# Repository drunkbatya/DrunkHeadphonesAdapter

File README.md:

# DrunkHeadphonesAdapter

## About

Yet another headphone adapter for mobile phones without 3.5mm jack..

I fucking hate the assholes who thought removing the headphone jack was a good idea.

This device integrated into a phone case and allows you to charge phone while listening to music. Charging is limited to 60-watt PD, USB PD Fast Role Swap is also supported, so theoretically, music playback shouldn't be interrupted when connecting or disconnecting the charger (currently untested).

The board has a physical switch that connects the phone USB data lines directly to the charger port. It also has two internal DIP switches: one to disable the microphone (by shorting Ring2 and Sleeve) and another to disable headphone detection.

The adapter uses readily available components and is designed for JLCPCB SMT assembly.

## Features
- CS43131 DAC with 24bit 96khz with independent oscillators for 24.576MHz and 22.5792MHz
- ES8327 codec with 24bit 48khz ADC only used for microphone
- STM32G0B1VCT6 acts as both USB-I2S converter and UCPD controller
- 60W PD with Fast Role Swap to prevent pausing music when connecting or disconnecting the charger
- Dual-role charger USB-C port, capable of both sinking and sourcing power
- CTIA headset pinout only, but pin 3 and 4 can be shorted via DIP switch
- Headset button decoding and forwarding to the phone as HID events
- UAC2+HID API, both Android and IOS are supported
- A lot of ESD protection on all external pins

## Firmware
HAL and arcitecture core is based on ported [Flipper Zero OS](https://github.com/flipperdevices/flipperzero-firmware)

### Building
```bash
git submodule update --init --recursive
make
```

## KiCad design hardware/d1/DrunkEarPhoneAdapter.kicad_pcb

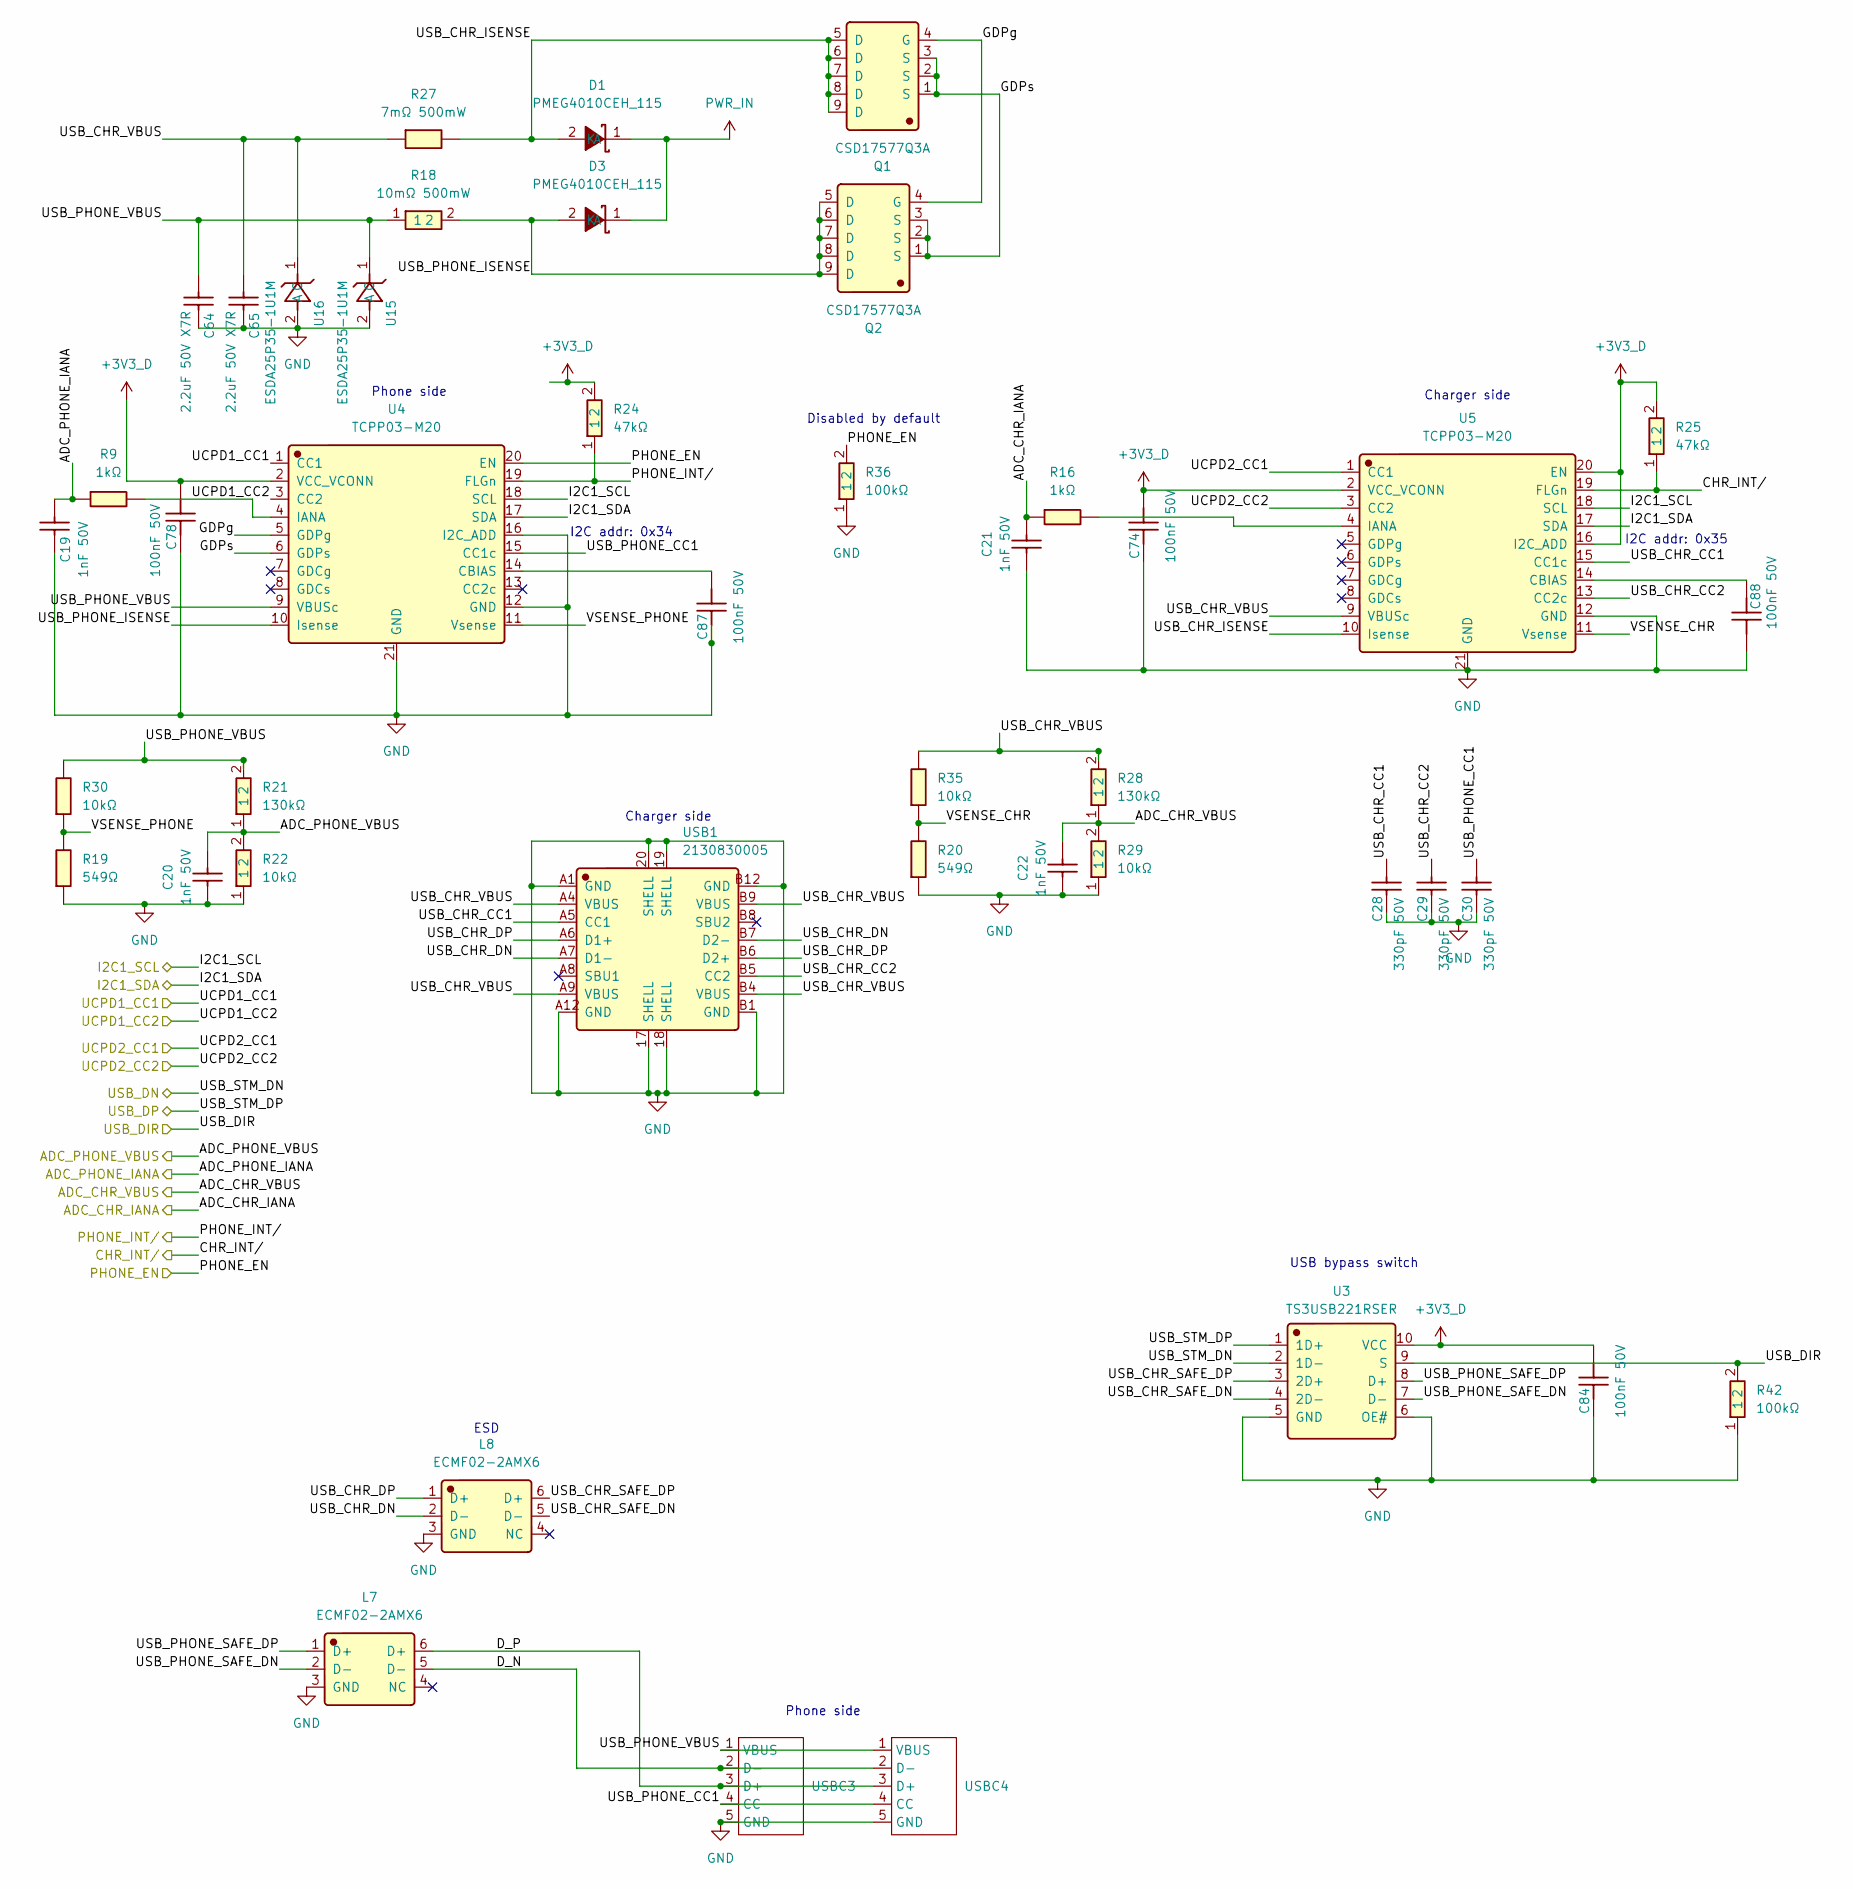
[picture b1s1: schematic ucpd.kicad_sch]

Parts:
C19, C20, C21, C22: 1nF 50V; C_0402_1005Metric; Manufacturer Part 0402B102K500NT; LCSC C1523
C28, C29, C30: 330pF 50V; C_0603_1608Metric; Manufacturer Part CL10C331JB8NNNC; LCSC C1664
C64, C65: 2.2uF 50V X7R; C_1206_3216Metric; Manufacturer Part CL31B225KBHNNNE; LCSC C50254
C74, C78, C84, C87, C88: 100nF 50V; C_0402_1005Metric; Manufacturer Part CL05B104KB54PNC; LCSC C307331
D1, D3: PMEG4010CEH_115; D_SOD-123F; Manufacturer Part PMEG4010CEH,115; LCSC C193342
L7, L8: ECMF02-2AMX6; Manufacturer Part ECMF02-2AMX6; LCSC C2651144
Q1, Q2: CSD17577Q3A; Manufacturer Part CSD17577Q3A; LCSC C201632
R9, R16: 1kΩ; R_0402_1005Metric; Manufacturer Part 0402WGF1001TCE; LCSC C11702
R18: 10mΩ 500mW; R_0805_2012Metric; Manufacturer Part ERJ6BWFR010V; LCSC C409060
R19, R20: 549Ω; R_0603_1608Metric; Manufacturer Part 0603WAF5490T5E; LCSC C23079
R21, R28: 130kΩ; R_0402_1005Metric; Manufacturer Part RC0402FR-07130KL; LCSC C93946
R22, R29: 10kΩ; R_0402_1005Metric; Manufacturer Part 0402WGF1002TCE; LCSC C25744
R24, R25: 47kΩ; R_0402_1005Metric; Manufacturer Part 0402WGF4702TCE; LCSC C25792
R27: 7mΩ 500mW; R_0805_2012Metric; Manufacturer Part HoYLR0805-1/2W-7mR-1%; LCSC C22450691
R30, R35: 10kΩ; R_0603_1608Metric; Manufacturer Part 0603WAF1002T5E; LCSC C25804
R36, R42: 100kΩ; 0402WGF1003TCE; Manufacturer Part 0402WGF1003TCE; LCSC C25741
U3: TS3USB221RSER; Manufacturer Part TS3USB221RSER; LCSC C130085
U4, U5: TCPP03-M20; Manufacturer Part TCPP03-M20; LCSC C3662955
U15, U16: ESDA25P35-1U1M; ESDA25P35-1U1M_C19829649; Manufacturer Part ESDA25P35-1U1M; LCSC C19829649
USB1: 2130830005; Manufacturer Part 2130830005; LCSC C2839029
USBC3, USBC4: USBC_EXT_5P

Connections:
+3V3_D: C74.2, C78.2, C84.2, R24.2, R25.2, U3.10 (VCC), U4.2 (VCC_VCONN), U5.2 (VCC_VCONN), U5.16 (I2C_ADD), U5.20 (EN); also elsewhere on the board
/adc/I2C_SCL: U4.18 (SCL), U5.18 (SCL); also elsewhere on the board
/adc/I2C_SDA: U4.17 (SDA), U5.17 (SDA); also elsewhere on the board
/mcu/ADC1_IN0: C19.2, R9.1; also elsewhere on the board
/mcu/ADC1_IN1: C20.2, R21.1, R22.2; also elsewhere on the board
/mcu/ADC1_IN2: C21.2, R16.1; also elsewhere on the board
/mcu/ADC1_IN3: C22.2, R28.1, R29.2; also elsewhere on the board
/mcu/GPIO_EXTI2: R24.1, U4.19 (FLGn); also elsewhere on the board
/mcu/GPIO_EXTI3: R25.1, U5.19 (FLGn); also elsewhere on the board
/mcu/PHONE_EN: R36.2, U4.20 (EN); also elsewhere on the board
/mcu/UCPD1_CC1: U4.1 (CC1); also elsewhere on the board
/mcu/UCPD1_CC2: U4.3 (CC2); also elsewhere on the board
/mcu/UCPD2_CC1: U5.1 (CC1); also elsewhere on the board
/mcu/UCPD2_CC2: U5.3 (CC2); also elsewhere on the board
/mcu/USB_DIR: R42.2, U3.9 (S); also elsewhere on the board
/mcu/USB_DN: U3.2 (1D-); also elsewhere on the board
/mcu/USB_DP: U3.1 (1D+); also elsewhere on the board
/ucpd/D_N: L7.5 (D-), USBC3.2 (D-), USBC4.2 (D-)
/ucpd/D_P: L7.6 (D+), USBC3.3 (D+), USBC4.3 (D+)
/ucpd/GDPg: Q1.4 (G), Q2.4 (G), U4.5 (GDPg)
/ucpd/GDPs: Q1.1 (S), Q1.2 (S), Q1.3 (S), Q2.1 (S), Q2.2 (S), Q2.3 (S), U4.6 (GDPs)
/ucpd/USB_CHR_CC1: C28.2, U5.15 (CC1c), USB1.A5 (CC1)
/ucpd/USB_CHR_CC2: C29.2, U5.13 (CC2c), USB1.B5 (CC2)
/ucpd/USB_CHR_DN: L8.2 (D-), USB1.A7 (D1-), USB1.B7 (D2-)
/ucpd/USB_CHR_DP: L8.1 (D+), USB1.A6 (D1+), USB1.B6 (D2+)
/ucpd/USB_CHR_ISENSE: D1.2 (A), Q1.5 (D), Q1.6 (D), Q1.7 (D), Q1.8 (D), Q1.9 (D), R27.2, U5.10 (Isense)
/ucpd/USB_CHR_SAFE_DN: L8.5 (D-), U3.4 (2D-)
/ucpd/USB_CHR_SAFE_DP: L8.6 (D+), U3.3 (2D+)
/ucpd/USB_CHR_VBUS: C65.2, R27.1, R28.2, R35.2, U5.9 (VBUSc), U16.1 (C), USB1.A4 (VBUS), USB1.A9 (VBUS), USB1.B4 (VBUS), USB1.B9 (VBUS)
/ucpd/USB_PHONE_CC1: C30.2, U4.15 (CC1c), USBC3.4 (CC), USBC4.4 (CC)
/ucpd/USB_PHONE_ISENSE: D3.2 (A), Q2.5 (D), Q2.6 (D), Q2.7 (D), Q2.8 (D), Q2.9 (D), R18.2, U4.10 (Isense)
/ucpd/USB_PHONE_SAFE_DN: L7.2 (D-), U3.7 (D-)
/ucpd/USB_PHONE_SAFE_DP: L7.1 (D+), U3.8 (D+)
/ucpd/USB_PHONE_VBUS: C64.2, R18.1, R21.2, R30.2, U4.9 (VBUSc), U15.1 (C), USBC3.1 (VBUS), USBC4.1 (VBUS)
/ucpd/VSENSE_CHR: R20.2, R35.1, U5.11 (Vsense)
/ucpd/VSENSE_PHONE: R19.2, R30.1, U4.11 (Vsense)
GND: C19.1, C20.1, C21.1, C22.1, C28.1, C29.1, C30.1, C64.1, C65.1, C74.1, C78.1, C84.1, C87.1, C88.2, L7.3 (GND), L8.3 (GND), R19.1, R20.1, R22.1, R29.1, R36.1, R42.1, U3.5 (GND), U3.6 (OE#), U4.12 (GND), U4.16 (I2C_ADD), U4.21 (GND), U5.12 (GND), U5.21 (GND), U15.2 (A), U16.2 (A), USB1.17 (SHELL), USB1.18 (SHELL), USB1.19 (SHELL), USB1.20 (SHELL), USB1.A1 (GND), USB1.A12 (GND), USB1.B1 (GND), USB1.B12 (GND), USBC3.5 (GND), USBC4.5 (GND); also elsewhere on the board
unnamed: C87.2, U4.14 (CBIAS)
unnamed: R9.2, U4.4 (IANA)
unnamed: C88.1, U5.14 (CBIAS)
unnamed: R16.2, U5.4 (IANA)
PWR_IN: D1.1 (K), D3.1 (K); also elsewhere on the board

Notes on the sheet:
I2C addr: 0x34
Charger side
I2C addr: 0x35
Disabled by default
USB bypass switch
Phone side
ESD

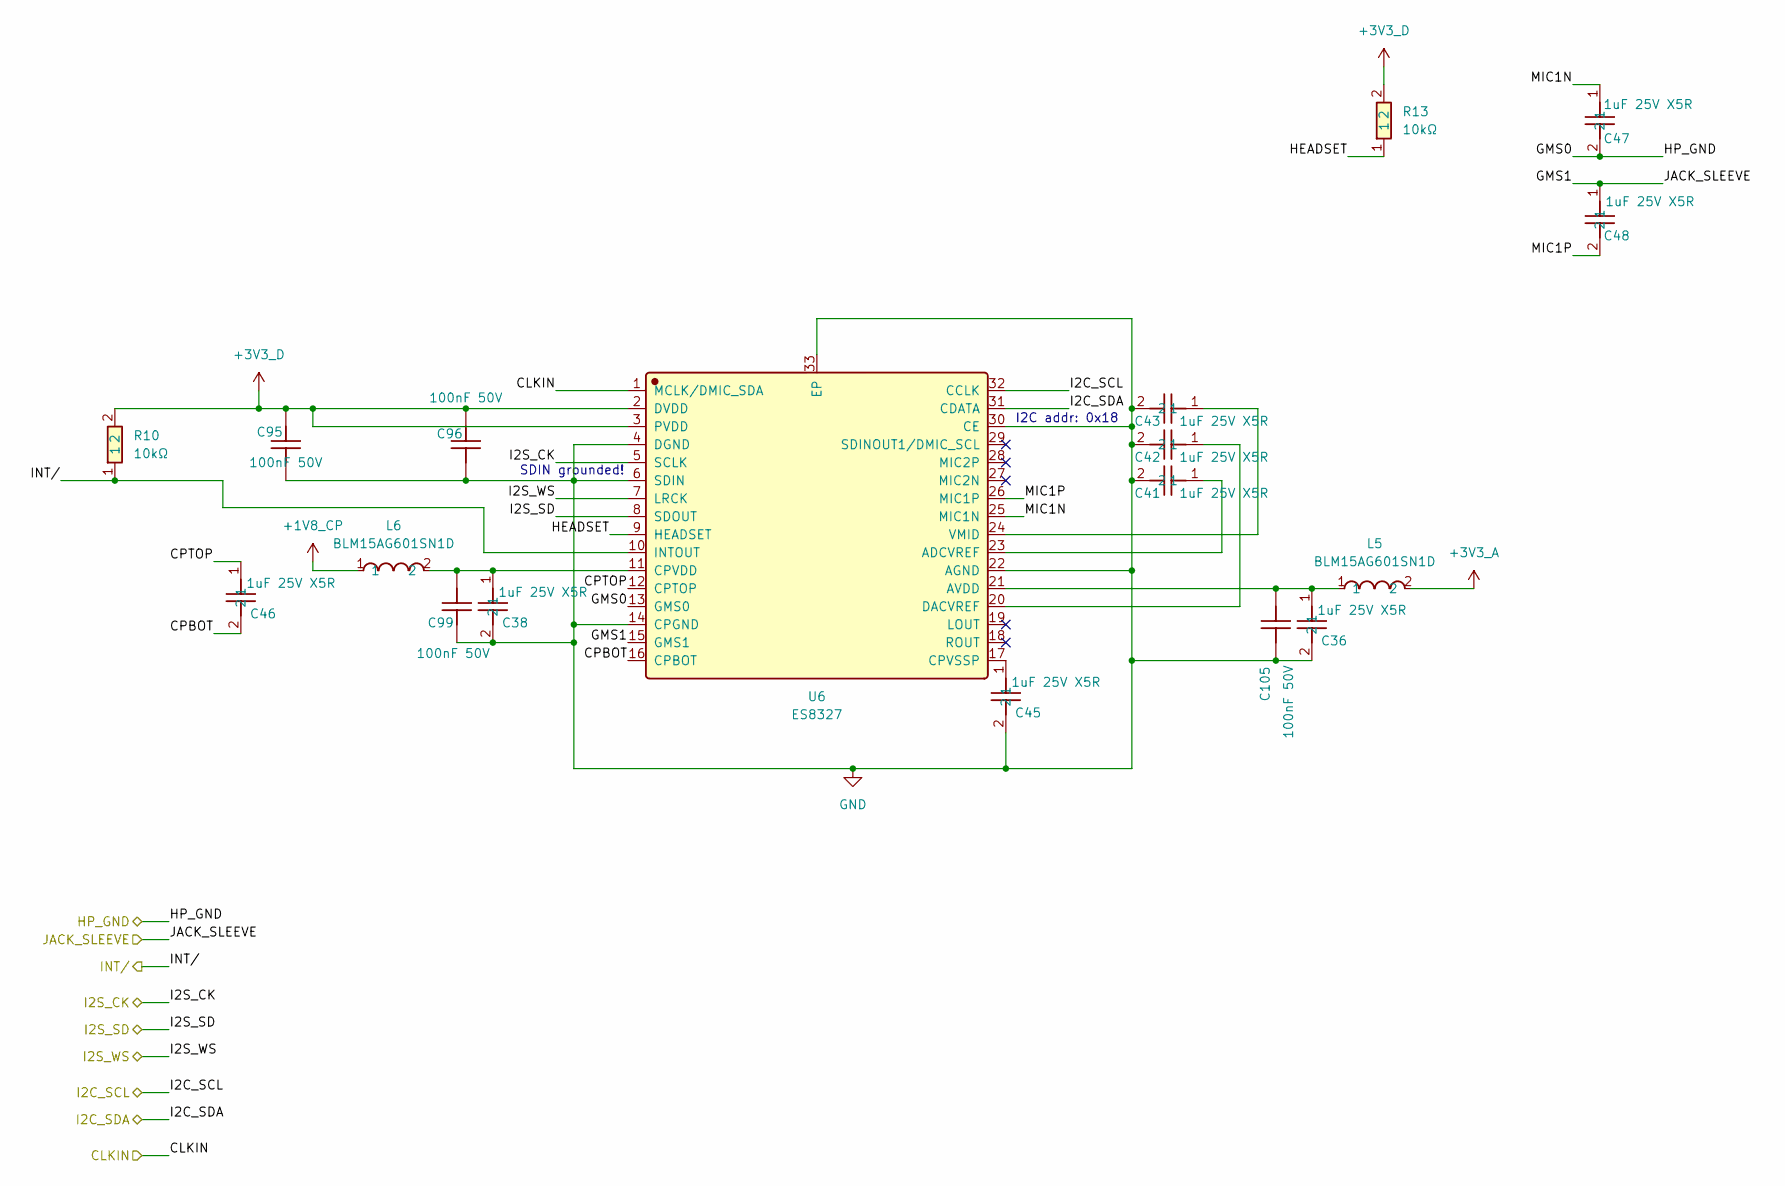
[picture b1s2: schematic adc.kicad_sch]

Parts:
C36, C38, C41, C42, C43, C45, C46, C47, C48: 1uF 25V X5R; CL05A105KA5NQNC; Manufacturer Part CL05A105KA5NQNC; LCSC C52923
C95, C96, C99, C105: 100nF 50V; C_0402_1005Metric; Manufacturer Part CL05B104KB54PNC; LCSC C307331
L5, L6: BLM15AG601SN1D; Manufacturer Part BLM15AG601SN1D; LCSC C76884
R10, R13: 10kΩ; R_0402_1005Metric; Manufacturer Part 0402WGF1002TCE; LCSC C25744
U6: ES8327; Manufacturer Part ES8327; LCSC C5145122

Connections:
+1V8_CP: L6.1; also elsewhere on the board
+3V3_A: L5.2; also elsewhere on the board
+3V3_D: C95.2, C96.2, R10.2, R13.2, U6.2 (DVDD), U6.3 (PVDD); also elsewhere on the board
/adc/CLKIN: U6.1 (MCLK/DMIC_SDA); also elsewhere on the board
/adc/CPBOT: C46.2, U6.16 (CPBOT)
/adc/CPTOP: C46.1, U6.12 (CPTOP)
/adc/GMS0: C47.2, U6.13 (GMS0); also elsewhere on the board
/adc/GMS1: C48.1, U6.15 (GMS1); also elsewhere on the board
/adc/HEADSET: R13.1, U6.9 (HEADSET)
/adc/I2C_SCL: U6.32 (CCLK); also elsewhere on the board
/adc/I2C_SDA: U6.31 (CDATA); also elsewhere on the board
/adc/I2S_CK: U6.5 (SCLK); also elsewhere on the board
/adc/I2S_SD: U6.8 (SDOUT); also elsewhere on the board
/adc/I2S_WS: U6.7 (LRCK); also elsewhere on the board
/adc/INT/: R10.1, U6.10 (INTOUT); also elsewhere on the board
/adc/MIC1N: C47.1, U6.25 (MIC1N)
/adc/MIC1P: C48.2, U6.26 (MIC1P)
GND: C36.2, C38.2, C41.2, C42.2, C43.2, C45.2, C95.1, C96.1, C99.1, C105.1, U6.4 (DGND), U6.6 (SDIN), U6.14 (CPGND), U6.22 (AGND), U6.30 (CE), U6.33 (EP); also elsewhere on the board
unnamed: C41.1, U6.23 (ADCVREF)
unnamed: C36.1, C105.2, L5.1, U6.21 (AVDD)
unnamed: C38.1, C99.2, L6.2, U6.11 (CPVDD)
unnamed: C45.1, U6.17 (CPVSSP)
unnamed: C42.1, U6.20 (DACVREF)
unnamed: C43.1, U6.24 (VMID)

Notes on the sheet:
SDIN grounded!
I2C addr: 0x18

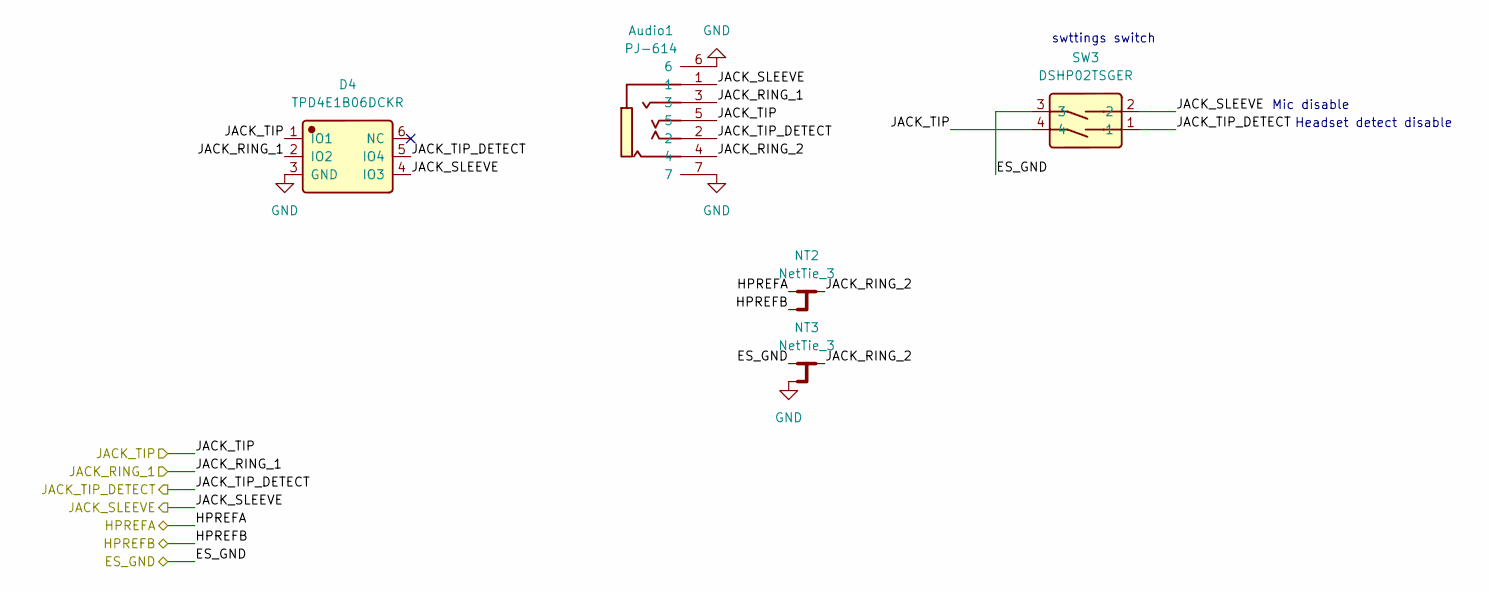
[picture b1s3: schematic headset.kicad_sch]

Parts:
Audio1: PJ-614; Manufacturer Part PJ-614; LCSC C145801
D4: TPD4E1B06DCKR; Manufacturer Part TPD4E1B06DCKR; LCSC C840093
NT2, NT3: NetTie_3; NetTie-3_SMD_Pad0.5mm
SW3: DSHP02TSGER; Manufacturer Part DSHP02TSGER; LCSC C3293142

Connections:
/adc/GMS0: NT3.1, SW3.3; also elsewhere on the board
/adc/GMS1: Audio1.1, D4.4 (IO3), SW3.2; also elsewhere on the board
/dac/HPREFA: NT2.1; also elsewhere on the board
/dac/HPREFB: NT2.3; also elsewhere on the board
/dac/JACK_RING_1: Audio1.3, D4.2 (IO2); also elsewhere on the board
/dac/JACK_TIP: Audio1.5, D4.1 (IO1), SW3.4; also elsewhere on the board
/dac/JACK_TIP_DETECT: Audio1.2, D4.5 (IO4), SW3.1; also elsewhere on the board
/headset/JACK_RING_2: Audio1.4, NT2.2, NT3.2
GND: Audio1.6, Audio1.7, D4.3 (GND), NT3.3; also elsewhere on the board

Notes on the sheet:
Headset detect disable
swttings switch
Mic disable

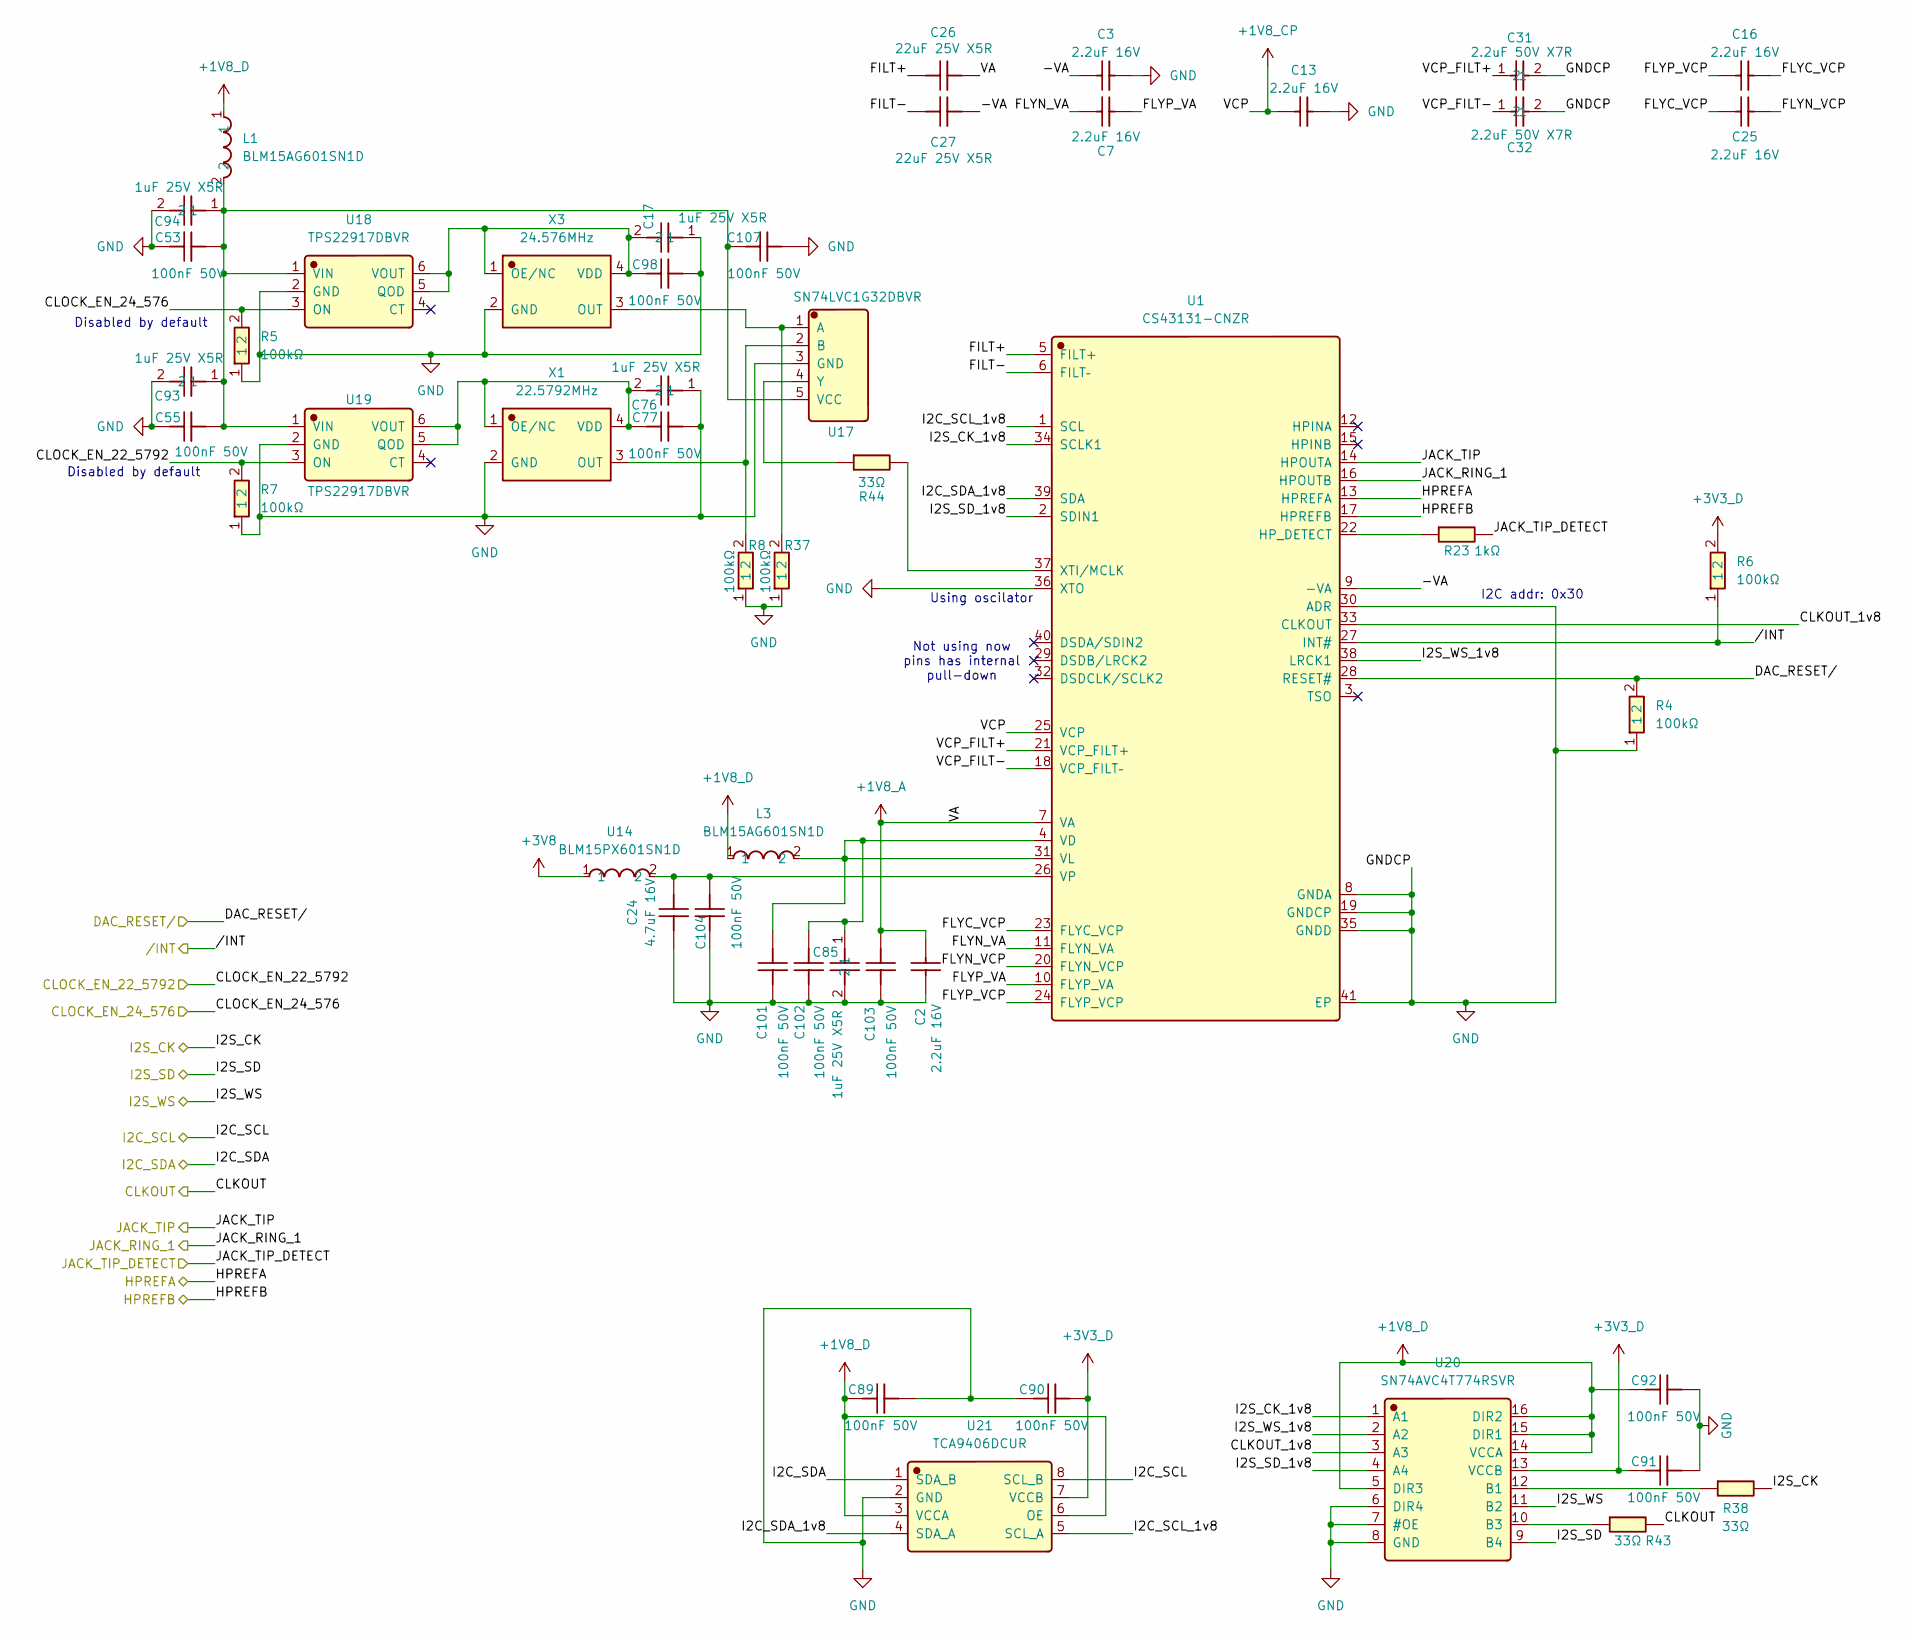
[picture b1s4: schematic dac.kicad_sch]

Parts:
C2, C3, C7, C13, C16, C25: 2.2uF 16V; C_0603_1608Metric; Manufacturer Part CL10A225KO8NNNC; LCSC C23630
C17, C76, C85, C93, C94: 1uF 25V X5R; CL05A105KA5NQNC; Manufacturer Part CL05A105KA5NQNC; LCSC C52923
C24: 4.7uF 16V; C_0603_1608Metric; Manufacturer Part CL10A475KO8NNNC; LCSC C19666
C26, C27: 22uF 25V X5R; CL21A226MAQNNNE; Manufacturer Part CL21A226MAQNNNE; LCSC C45783
C31, C32: 2.2uF 50V X7R; CC0805KKX7R9BB225; Manufacturer Part CC0805KKX7R9BB225; LCSC C125847
C53, C55, C77, C89, C90, C91, C92, C98, C101, C102, C103, C104, C107: 100nF 50V; C_0402_1005Metric; Manufacturer Part CL05B104KB54PNC; LCSC C307331
L1, L3: BLM15AG601SN1D; Manufacturer Part BLM15AG601SN1D; LCSC C76884
R4, R5, R6, R7, R8, R37: 100kΩ; 0402WGF1003TCE; Manufacturer Part 0402WGF1003TCE; LCSC C25741
R23: 1kΩ; R_0402_1005Metric; Manufacturer Part 0402WGF1001TCE; LCSC C11702
R38, R43, R44: 33Ω; R_0402_1005Metric; Manufacturer Part 0402WGF330JTCE; LCSC C25105
U1: CS43131-CNZR; Manufacturer Part CS43131-CNZR; LCSC C965907
U14: BLM15PX601SN1D; Manufacturer Part BLM15PX601SN1D; LCSC C160977
U17: SN74LVC1G32DBVR; SOT-23-5; Manufacturer Part SN74LVC1G32DBVR; LCSC C10096
U18, U19: TPS22917DBVR; Manufacturer Part TPS22917DBVR; LCSC C2681320
U20: SN74AVC4T774RSVR; Manufacturer Part SN74AVC4T774RSVR; LCSC C779392
U21: TCA9406DCUR; Manufacturer Part TCA9406DCUR; LCSC C840107
X1: 22.5792MHz; SX2M22_5792M20F30TNN; Manufacturer Part SX2M22.5792M20F30TNN; LCSC C5452663
X3: 24.576MHz; SX2M22_5792M20F30TNN; Manufacturer Part SX2M24.576M20F30TNN; LCSC C5452664

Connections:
+1V8_A: C2.2, C26.2, C103.2, U1.7 (VA); also elsewhere on the board
+1V8_CP: C13.1, U1.25 (VCP); also elsewhere on the board
+1V8_D: C89.1, C92.1, L1.1, L3.1, U20.5 (DIR3), U20.14 (VCCA), U20.15 (DIR1), U20.16 (DIR2), U21.3 (VCCA), U21.6 (OE); also elsewhere on the board
+3V3_D: C90.2, C91.1, R6.2, U20.13 (VCCB), U21.7 (VCCB); also elsewhere on the board
+3V8: U14.1; also elsewhere on the board
/adc/CLKIN: R43.2; also elsewhere on the board
/adc/I2C_SCL: U21.8 (SCL_B); also elsewhere on the board
/adc/I2C_SDA: U21.1 (SDA_B); also elsewhere on the board
/dac/-VA: C3.1, C27.2, U1.9 (-VA)
/dac/CLKOUT_1v8: U1.33 (CLKOUT), U20.3 (A3)
/dac/CLOCK_EN_22_5792: R7.2, U19.3 (ON); also elsewhere on the board
/dac/CLOCK_EN_24_576: R5.2, U18.3 (ON); also elsewhere on the board
/dac/DAC_RESET/: R4.2, U1.28 (RESET#); also elsewhere on the board
/dac/FILT+: C26.1, U1.5 (FILT+)
/dac/FILT-: C27.1, U1.6 (FILT–)
/dac/FLYC_VCP: C16.2, C25.1, U1.23 (FLYC_VCP)
/dac/FLYN_VA: C7.1, U1.11 (FLYN_VA)
/dac/FLYN_VCP: C25.2, U1.20 (FLYN_VCP)
/dac/FLYP_VA: C7.2, U1.10 (FLYP_VA)
/dac/FLYP_VCP: C16.1, U1.24 (FLYP_VCP)
/dac/HPREFA: U1.13 (HPREFA); also elsewhere on the board
/dac/HPREFB: U1.17 (HPREFB); also elsewhere on the board
/dac/I2C_SCL_1v8: U1.1 (SCL), U21.5 (SCL_A)
/dac/I2C_SDA_1v8: U1.39 (SDA), U21.4 (SDA_A)
/dac/I2S_CK: R38.2; also elsewhere on the board
/dac/I2S_CK_1v8: U1.34 (SCLK1), U20.1 (A1)
/dac/I2S_SD: U20.9 (B4); also elsewhere on the board
/dac/I2S_SD_1v8: U1.2 (SDIN1), U20.4 (A4)
/dac/I2S_WS: U20.11 (B2); also elsewhere on the board
/dac/I2S_WS_1v8: U1.38 (LRCK1), U20.2 (A2)
/dac/JACK_RING_1: U1.16 (HPOUTB); also elsewhere on the board
/dac/JACK_TIP: U1.14 (HPOUTA); also elsewhere on the board
/dac/JACK_TIP_DETECT: R23.2; also elsewhere on the board
/dac/VCP_FILT+: C31.1, U1.21 (VCP_FILT+)
/dac/VCP_FILT-: C32.1, U1.18 (VCP_FILT–)
/dac//INT: R6.1, U1.27 (INT#); also elsewhere on the board
GND: C2.1, C3.2, C13.2, C17.1, C24.1, C31.2, C32.2, C53.1, C55.1, C76.1, C77.2, C85.2, C89.2, C90.1, C91.2, C92.2, C93.2, C94.2, C98.2, C101.1, C102.1, C103.1, C104.1, C107.2, R4.1, R5.1, R7.1, R8.1, R37.1, U1.8 (GNDA), U1.19 (GNDCP), U1.30 (ADR), U1.35 (GNDD), U1.36 (XTO), U1.41 (EP), U17.3 (GND), U18.2 (GND), U19.2 (GND), U20.6 (DIR4), U20.7 (#OE), U20.8 (GND), U21.2 (GND), X1.2 (GND), X3.2 (GND); also elsewhere on the board
unnamed: R23.1, U1.22 (HP_DETECT)
unnamed: C85.1, C101.2, C102.2, L3.2, U1.4 (VD), U1.31 (VL)
unnamed: C24.2, C104.2, U1.26 (VP), U14.2
unnamed: R44.2, U1.37 (XTI/MCLK)
unnamed: R37.2, U17.1 (A), X3.3 (OUT)
unnamed: R8.2, U17.2 (B), X1.3 (OUT)
unnamed: C53.2, C55.2, C93.1, C94.1, C107.1, L1.2, U17.5 (VCC), U18.1 (VIN), U19.1 (VIN)
unnamed: R44.1, U17.4 (Y)
unnamed: C17.2, C98.1, U18.5 (QOD), U18.6 (VOUT), X3.1 (OE/NC), X3.4 (VDD)
unnamed: C76.2, C77.1, U19.5 (QOD), U19.6 (VOUT), X1.1 (OE/NC), X1.4 (VDD)
unnamed: R38.1, U20.12 (B1)
unnamed: R43.1, U20.10 (B3)

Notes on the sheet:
I2C addr: 0x30
Using oscilator
Not using now pins has internal pull-down
Disabled by default

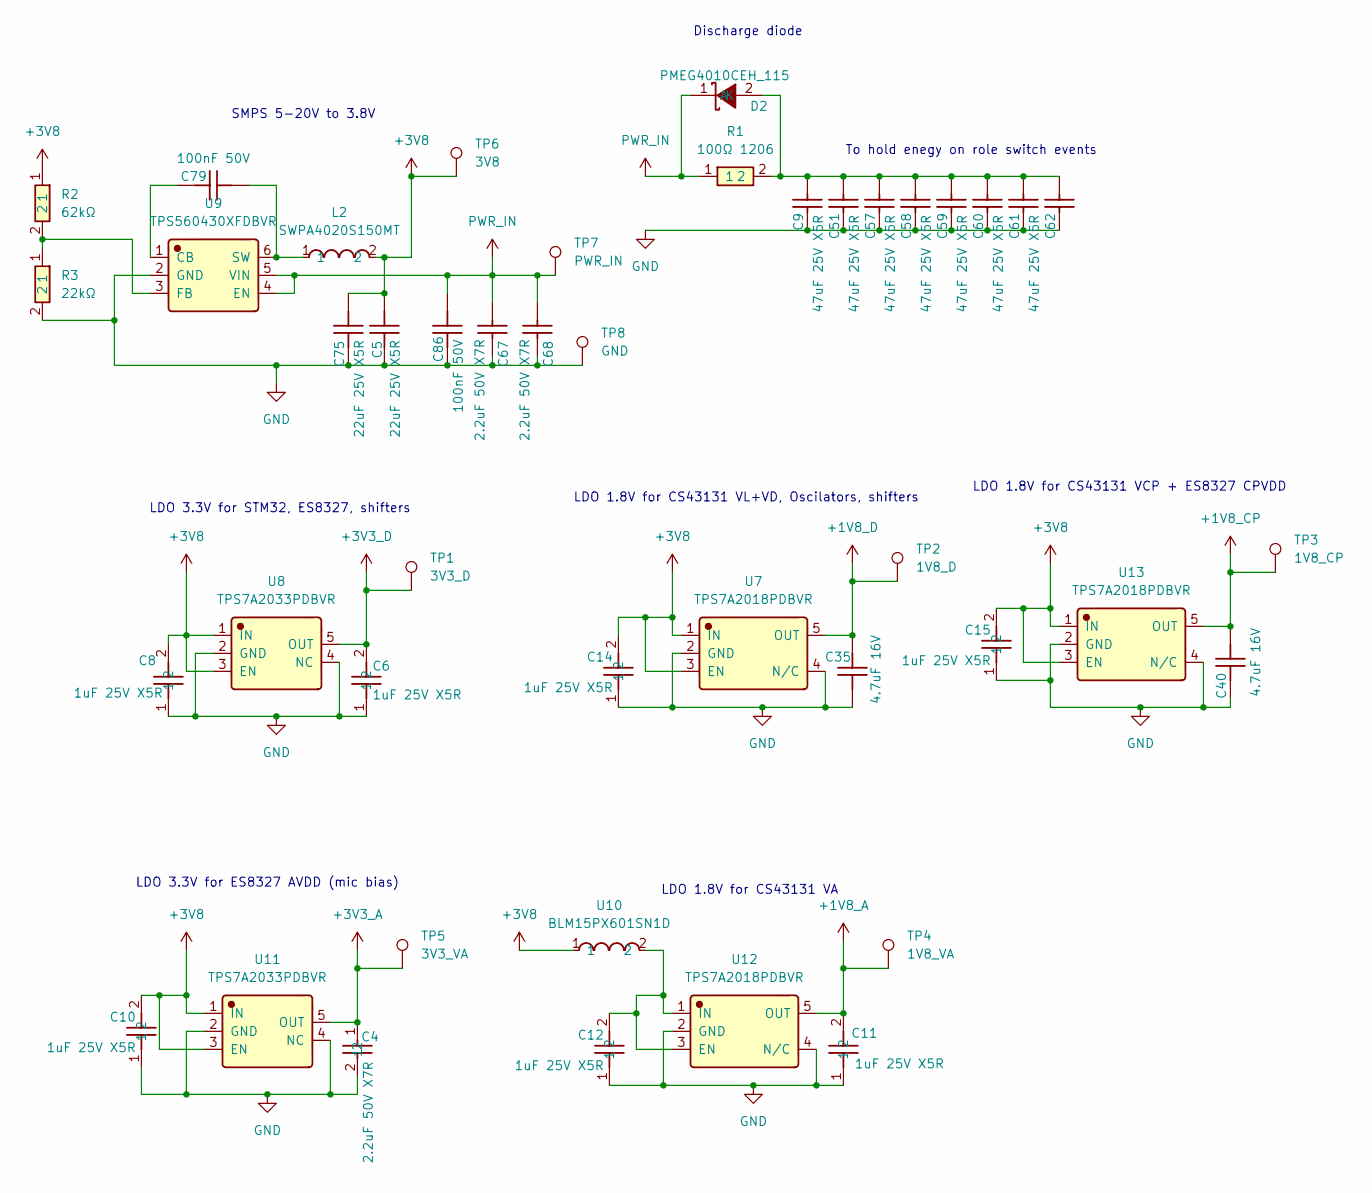
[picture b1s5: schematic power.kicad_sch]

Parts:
C4: 2.2uF 50V X7R; CC0805KKX7R9BB225; Manufacturer Part CC0805KKX7R9BB225; LCSC C125847
C5, C75: 22uF 25V X5R; CL21A226MAQNNNE; Manufacturer Part CL21A226MAQNNNE; LCSC C45783
C6, C8, C10, C11, C12, C14, C15: 1uF 25V X5R; CL05A105KA5NQNC; Manufacturer Part CL05A105KA5NQNC; LCSC C52923
C9, C51, C57, C58, C59, C60, C61, C62: 47uF 25V X5R; C_1206_3216Metric; Manufacturer Part C3216X5R1E476MTJ00E; LCSC C76659
C35, C40: 4.7uF 16V; C_0603_1608Metric; Manufacturer Part CL10A475KO8NNNC; LCSC C19666
C67, C68: 2.2uF 50V X7R; C_1206_3216Metric; Manufacturer Part CL31B225KBHNNNE; LCSC C50254
C79, C86: 100nF 50V; C_0402_1005Metric; Manufacturer Part CL05B104KB54PNC; LCSC C307331
D2: PMEG4010CEH_115; D_SOD-123F; Manufacturer Part PMEG4010CEH,115; LCSC C193342
L2: SWPA4020S150MT; Manufacturer Part SWPA4020S150MT; LCSC C36407
R1: 100Ω 1206; R_1206_3216Metric; Manufacturer Part SR1206JR-7W100RL; LCSC C874066
R2: 62kΩ; 0402WGF6202TCE; Manufacturer Part 0402WGF6202TCE; LCSC C37825
R3: 22kΩ; 0402WGF2202TCE; Manufacturer Part 0402WGF2202TCE; LCSC C25768
TP1: 3V3_D; TestPoint_Pad_1.0x1.0mm
TP2: 1V8_D; TestPoint_Pad_1.0x1.0mm
TP3: 1V8_CP; TestPoint_Pad_1.0x1.0mm
TP4: 1V8_VA; TestPoint_Pad_1.0x1.0mm
TP5: 3V3_VA; TestPoint_Pad_1.0x1.0mm
TP6: 3V8; TestPoint_Pad_1.0x1.0mm
TP7: PWR_IN; TestPoint_Pad_1.0x1.0mm
TP8: GND; TestPoint_Pad_1.0x1.0mm
U7, U12, U13: TPS7A2018PDBVR; Manufacturer Part TPS7A2018PDBVR; LCSC C963430
U8, U11: TPS7A2033PDBVR; Manufacturer Part TPS7A2033PDBVR; LCSC C2862740
U9: TPS560430XFDBVR; Manufacturer Part TPS560430XFDBVR; LCSC C523980
U10: BLM15PX601SN1D; Manufacturer Part BLM15PX601SN1D; LCSC C160977

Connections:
+1V8_A: C11.2, TP4.1 (1_1), U12.5 (OUT); also elsewhere on the board
+1V8_CP: C40.2, TP3.1 (1_1), U13.5 (OUT); also elsewhere on the board
+1V8_D: C35.2, TP2.1 (1_1), U7.5 (OUT); also elsewhere on the board
+3V3_A: C4.1, TP5.1 (1_1), U11.5 (OUT); also elsewhere on the board
+3V3_D: C6.2, TP1.1 (1_1), U8.5 (OUT); also elsewhere on the board
+3V8: C5.1, C8.2, C10.2, C14.2, C15.2, C75.1, L2.2, R2.1, TP6.1 (1_1), U7.1 (IN), U7.3 (EN), U8.1 (IN), U8.3 (EN), U10.1, U11.1 (IN), U11.3 (EN), U13.1 (IN), U13.3 (EN); also elsewhere on the board
GND: C4.2, C5.2, C6.1, C8.1, C9.1, C10.1, C11.1, C12.1, C14.1, C15.1, C35.1, C40.1, C51.1, C57.1, C58.1, C59.1, C60.1, C61.1, C62.1, C67.1, C68.1, C75.2, C86.1, R3.2, TP8.1 (1_1), U7.2 (GND), U7.4 (N/C), U8.2 (GND), U8.4 (NC), U9.2 (GND), U11.2 (GND), U11.4 (NC), U12.2 (GND), U12.4 (N/C), U13.2 (GND), U13.4 (N/C); also elsewhere on the board
unnamed: C9.2, C51.2, C57.2, C58.2, C59.2, C60.2, C61.2, C62.2, D2.2 (A), R1.2
unnamed: C79.1, U9.1 (CB)
unnamed: R2.2, R3.1, U9.3 (FB)
unnamed: C79.2, L2.1, U9.6 (SW)
unnamed: C12.2, U10.2, U12.1 (IN), U12.3 (EN)
PWR_IN: C67.2, C68.2, C86.2, D2.1 (K), R1.1, TP7.1 (1_1), U9.4 (EN), U9.5 (VIN); also elsewhere on the board

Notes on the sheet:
LDO 1.8V for CS43131 VCP + ES8327 CPVDD
LDO 3.3V for STM32, ES8327, shifters
To hold enegy on role switch events
LDO 3.3V for ES8327 AVDD (mic bias)
Discharge diode
LDO 1.8V for CS43131 VL+VD, Oscilators, shifters
LDO 1.8V for CS43131 VA
SMPS 5-20V to 3.8V
